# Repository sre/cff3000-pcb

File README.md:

CFF3000 GPIO interface
======================

This repository contains information how to interface a Abus CFF3000
remote control with a Raspberry Pi or similar development board using
GPIOs. First of all one needs to disassemble the remote control. Be
careful when removing the rubber part from the PCB to avoid tearing
off the antenna.

Next step: Soldering a couple of wires. I tried to tap the signals
at locations, that are as simple to solder as possible. Unfortunately
tapping the LEDs is a bit tricky. Note, that the CFF3000 design is
"interesting" and does not use a common ground/vcc for the buttons
and LEDs.

To work around the problem with uncommon ground/vcc, I made a small
single layer PCB. Some explanations for the schematics: The CFF3000
is connected on the right side of the schematics. Each buttons is
connected to a opto-coupler, the other side of the opto-coupler is
connected to the computer's GPIO through a resistor as current limiter.
The LEDs are also connected to a opto-coupler, but the signal is
additionally inverted and cleaned by a schmitt-trigger. This was
necessary for proper reading of the green LED. Also the green LED
channel has a 100Hz RC lowpass filter (47nF, 33K), since it is driven
with a 1KHz PWM signal by the CFF3000 and we want a logical 1 or 0
instead.

License
=======

© 2018 Sebastian Reichel

ISC License

Permission to use, copy, modify, and/or distribute this software for
any purpose with or without fee is hereby granted, provided that the
above copyright notice and this permission notice appear in all copies.

THE SOFTWARE IS PROVIDED "AS IS" AND THE AUTHOR DISCLAIMS ALL WARRANTIES
WITH REGARD TO THIS SOFTWARE INCLUDING ALL IMPLIED WARRANTIES OF
MERCHANTABILITY AND FITNESS. IN NO EVENT SHALL THE AUTHOR BE LIABLE FOR
ANY SPECIAL, DIRECT, INDIRECT, OR CONSEQUENTIAL DAMAGES OR ANY DAMAGES
WHATSOEVER RESULTING FROM LOSS OF USE, DATA OR PROFITS, WHETHER IN AN
ACTION OF CONTRACT, NEGLIGENCE OR OTHER TORTIOUS ACTION, ARISING OUT OF
OR IN CONNECTION WITH THE USE OR PERFORMANCE OF THIS SOFTWARE.

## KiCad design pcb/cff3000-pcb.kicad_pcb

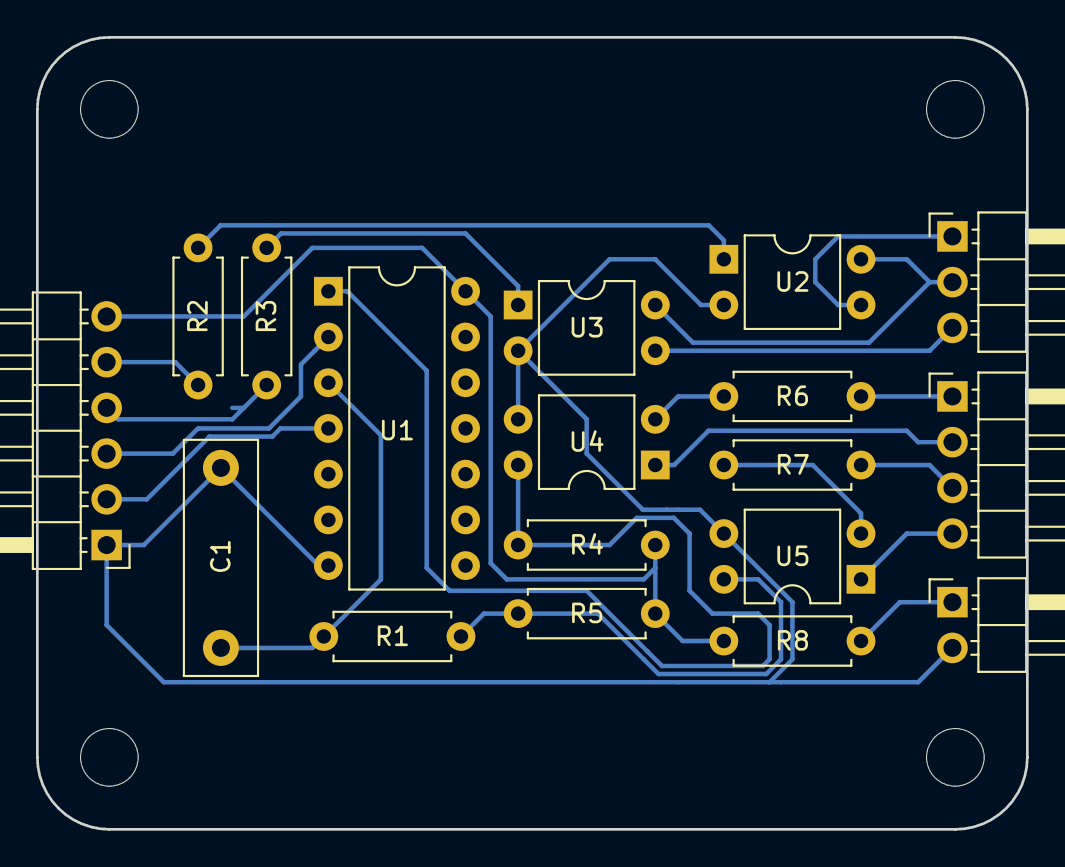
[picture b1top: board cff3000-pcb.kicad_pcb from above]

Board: 2 copper layers, 55.0 x 44.0 mm, 22 parts (0 on the bottom side), 21 nets.

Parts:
C1: 47nF; C_Rect_L13.0mm_W4.0mm_P10.00mm_FKS3_FKP3_MKS4
J1: Conn_01x03; PinHeader_1x03_P2.54mm_Horizontal
J2: Conn_01x04; PinHeader_1x04_P2.54mm_Horizontal
J3: Conn_01x06; PinHeader_1x06_P2.54mm_Horizontal
J4: Conn_01x02; PinHeader_1x02_P2.54mm_Horizontal
MK1, MK2, MK3, MK4: Mounting_Hole; MountingHole_3.2mm_M3
R1: 33K; R_Axial_DIN0207_L6.3mm_D2.5mm_P7.62mm_Horizontal
R2, R3, R4, R5: 1K; R_Axial_DIN0207_L6.3mm_D2.5mm_P7.62mm_Horizontal
R6, R7: 82; R_Axial_DIN0207_L6.3mm_D2.5mm_P7.62mm_Horizontal
R8: 0; R_Axial_DIN0207_L6.3mm_D2.5mm_P7.62mm_Horizontal
U1: 74HC14; DIP-14_W7.62mm
U2, U3, U4, U5: PC817; DIP-4_W7.62mm

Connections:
/BUTTONS+: J1.2, U2.4, U3.4
/GPIO_GREEN: J3.2, U1.4
/GPIO_LOCK: J3.4, R3.2
/GPIO_RED: J3.3, U1.2
/GPIO_UNLOCK: J3.5, R2.2
/GREEN+: J2.4, U5.1
/GREEN-: J2.3, R7.1
/LOCK: J1.3, U3.3
/RED+: J2.2, U4.1
/RED-: J2.1, R6.1
/UNLOCK: J1.1, U2.3
GND: C1.2, J3.1, J4.2, U1.7, U2.2, U3.2, U4.3, U5.3
unnamed: C1.1, R1.1, U1.3
unnamed: J4.1, R8.1
unnamed: R1.2, R5.1, U5.4
unnamed: R2.1, U2.1
unnamed: R3.1, U3.1
unnamed: R4.1, U1.1, U4.4
unnamed: R6.2, U4.2
unnamed: R7.2, U5.2
VCC: J3.6, R4.2, R5.2, R8.2, U1.14
